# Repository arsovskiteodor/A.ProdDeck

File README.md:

# ProdDeck

Custom PCB productivity deck — StreamDeck-style device with key switches, rotary encoders, and a slider. Targets editors, designers, and video editors.

A joint project with product design student **Aleksandra Elin** ([LinkedIn](https://www.linkedin.com/in/aleksandra-elin-6274052a9/)).

**Hardware:**
- 6x key switches — Gateron KS-33 (Low Profile 2.0)
- 3x rotary encoders with push button — Bourns PEC11R-4220F-S0024
- 1x slider (fader) — Bourns PTA6043-2015DPB103
- MCU — STM32WB55CGU6 (BLE + native USB)
- USB-C (wired HID + charging) and LiPo battery (wireless BLE HID)

## PCB

| 3D view (top) | Layout |
|---|---|
|  |  |

## Repository Layout

| Folder | Contents |
|---|---|
| `KiCAD/ProdDeck/` | Schematic and PCB layout (KiCad 10), project libraries in `libs/`, fabrication outputs in `fab/` |
| `firmware/` | MCU firmware (ZMK) |
| `app/` | Desktop configurator — maps keys/dials/slider to shortcuts and app profiles |
| `enclosure/` | 3D mechanical files for chassis/panel |
| `docs/` | Component specs, schematic plan, datasheet notes |

## Status

| Area | Status |
|---|---|
| Component selection | Done |
| Schematic | Done |
| PCB layout | Done — 4-layer, 117 x 77 mm, fully routed, DRC clean |
| Fabrication outputs | Generated — Gerbers, drill, BOM and JLCPCB CPL in `KiCAD/ProdDeck/fab/` |
| Firmware | Not started — framework chosen (ZMK); board definition still to be written |
| Configurator app | Not started — stack not yet decided (Tauri vs Electron) |
| Enclosure | Not started — CAD tool not yet decided |

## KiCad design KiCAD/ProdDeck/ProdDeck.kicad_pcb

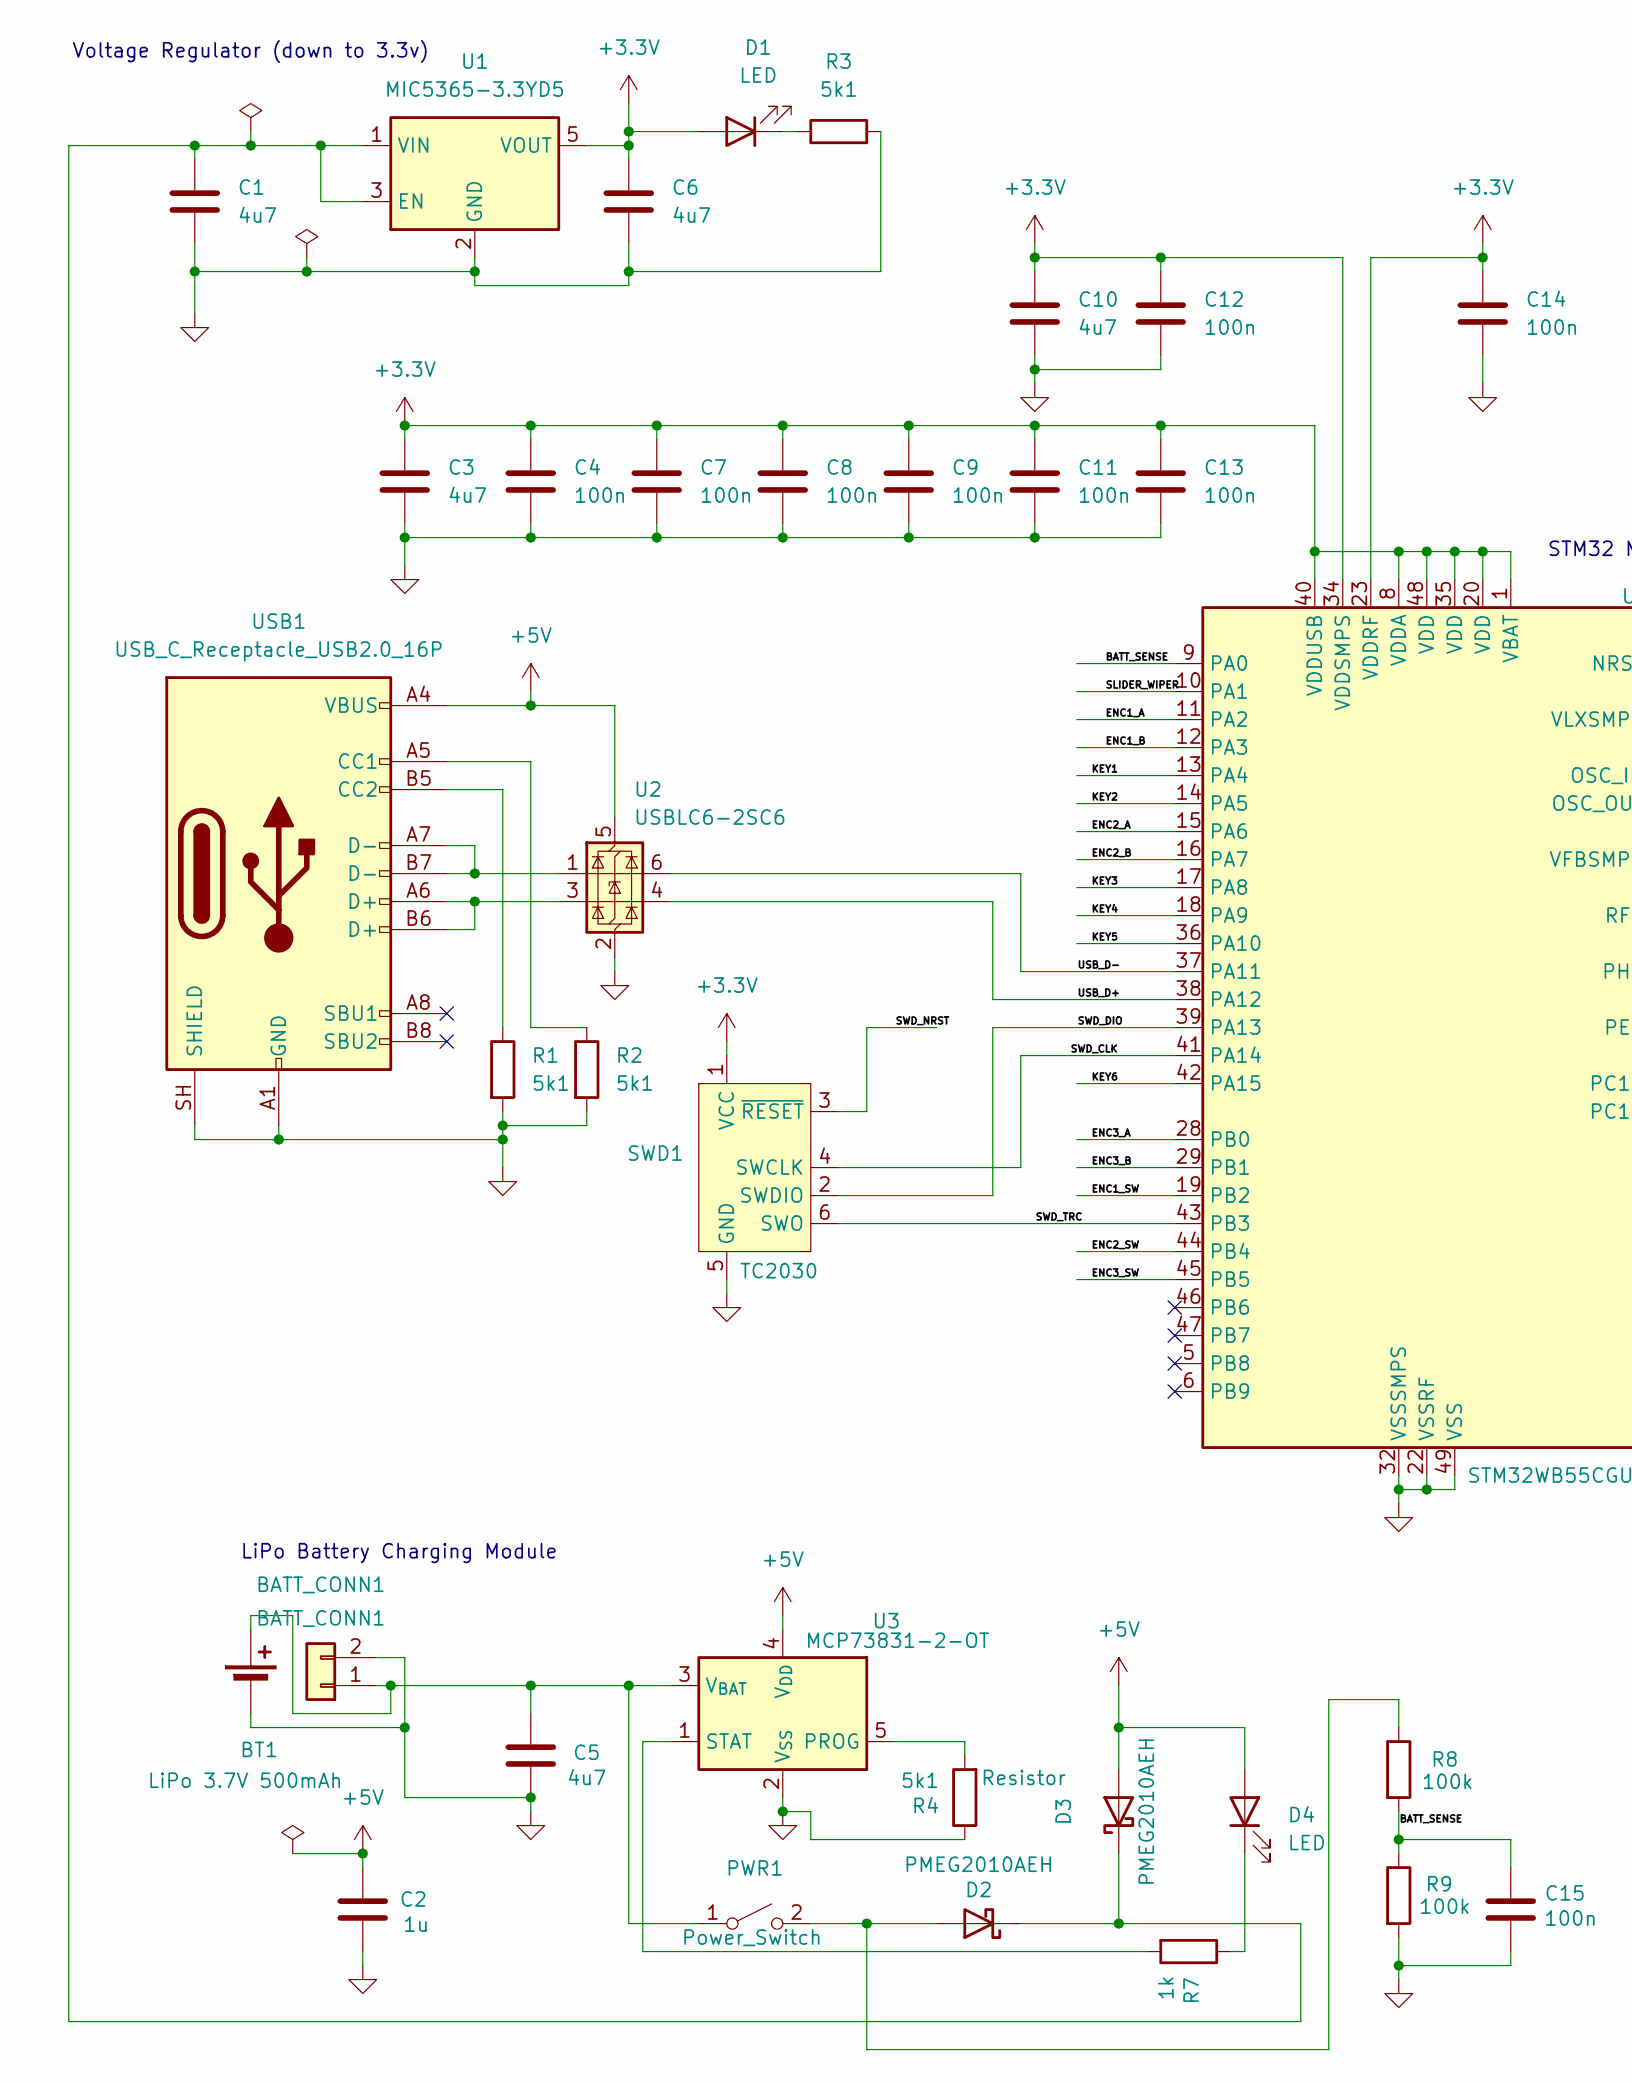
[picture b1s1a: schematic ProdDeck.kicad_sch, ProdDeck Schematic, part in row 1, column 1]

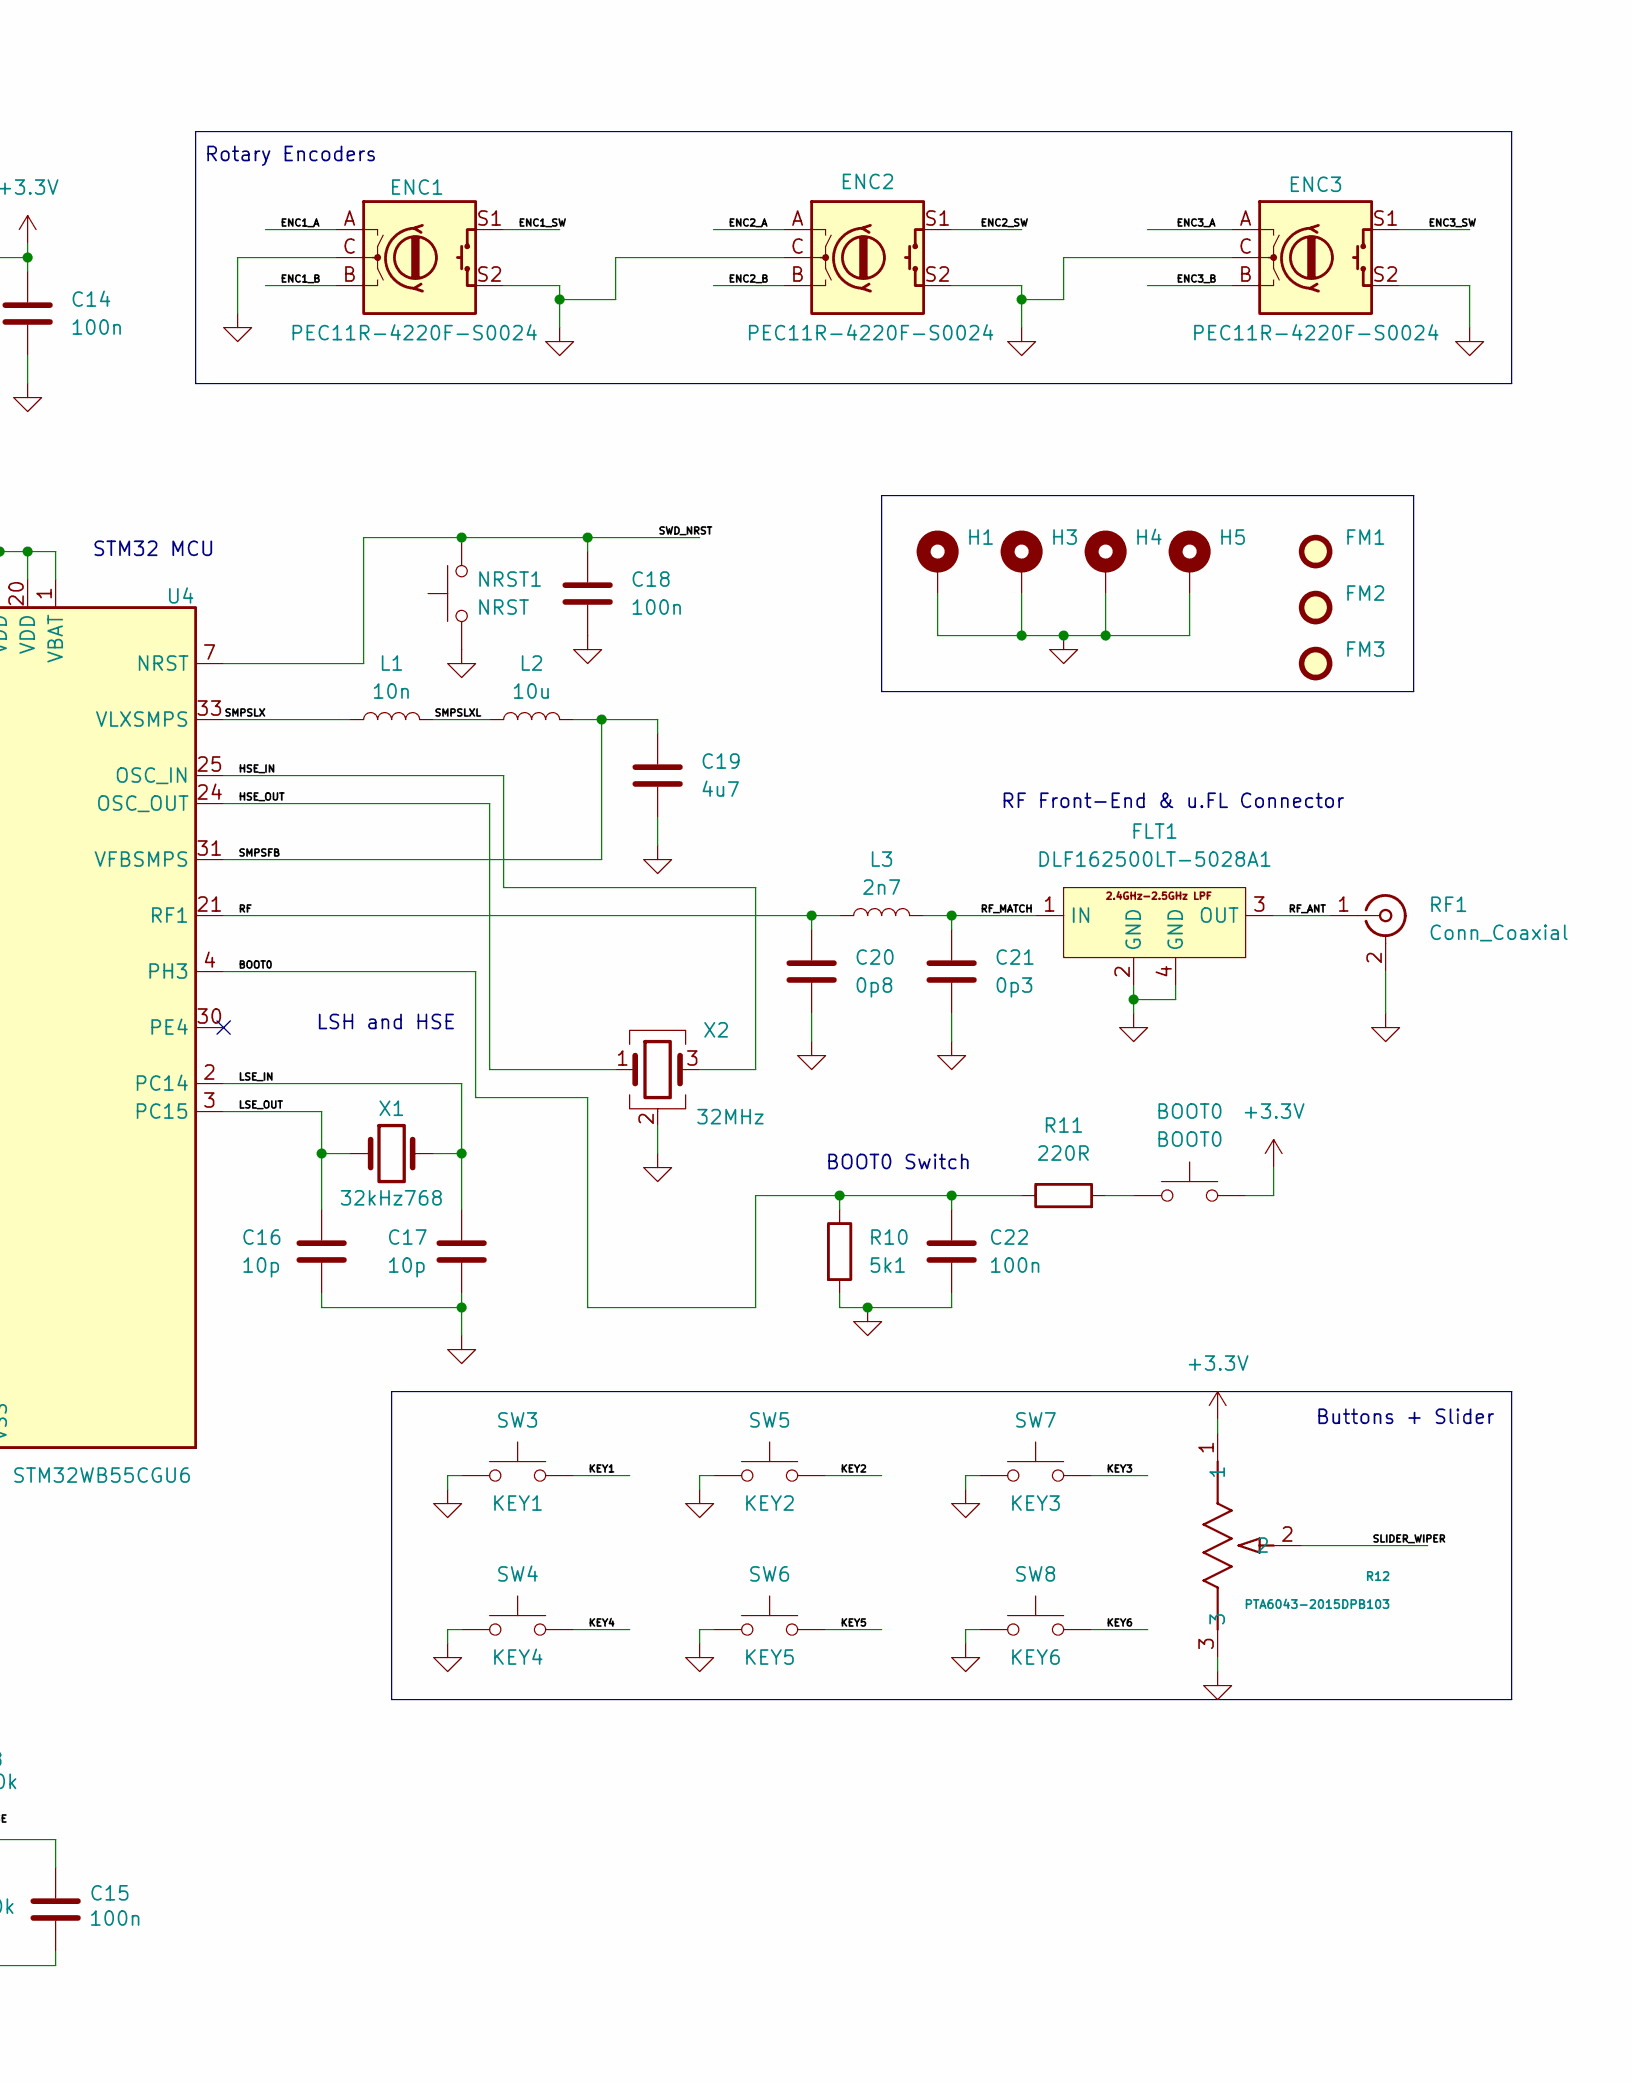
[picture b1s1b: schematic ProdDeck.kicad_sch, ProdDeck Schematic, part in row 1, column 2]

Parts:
BATT_CONN1: BATT_CONN1; JST_PH_S2B-PH-K_1x02_P2.00mm_Horizontal; Manufacturer Part Number S2B-PH-K-S(LF)(SN)
BOOT0: BOOT0; SW_SPST_CK_RS282G05A3; Manufacturer Part Number RS-282G05A3-SM RT
BT1: LiPo 3.7V 500mAh
C1, C3, C5, C6, C10, C19: 4u7; C_0603_1608Metric; Manufacturer Part Number 0603YD475MAT2A
C2: 1u; C_0402_1005Metric; Manufacturer Part Number 0402ZD105KAT2A
C4, C7, C8, C9, C11, C12, C13, C14, C15, C18, C22: 100n; C_0402_1005Metric; Manufacturer Part Number 04023C104KAT2A
C16, C17: 10p; C_0402_1005Metric; Manufacturer Part Number 04025A100JAT4A
C20: 0p8; C_0402_1005Metric; Manufacturer Part Number GRM1555C1HR80BA01D
C21: 0p3; C_0402_1005Metric; Manufacturer Part Number GRM1555C1HR30WA01D
D1, D4: LED; LED_0402_1005Metric; Manufacturer Part Number 150040RS73240
D2, D3: PMEG2010AEH; D_SOD-123; Manufacturer Part Number PMEG2010AEH,115
ENC1, ENC2, ENC3: PEC11R-4220F-S0024; Bourns-PEC11R-4220F-S0024-0-0-0
FLT1: DLF162500LT-5028A1; Manufacturer Part Number DLF162500LT-5028A1
FM1, FM2, FM3: Fiducial; Fiducial_1mm_Mask2mm
H1, H3, H4, H5: MountingHole_Pad; MountingHole_3.2mm_M3_Pad
L1: 10n; L_0402_1005Metric; Manufacturer Part Number LQG15WZ10NJ02D
L2: 10u; L_0805_2012Metric; Manufacturer Part Number LQM21FN100M80L
L3: 2n7; L_0402_1005Metric; Manufacturer Part Number LQG15HS2N7S02D
NRST1: NRST; SW_SPST_CK_RS282G05A3; Manufacturer Part Number RS-282G05A3-SM RT
PWR1: Power_Switch; SW_Slide_SPDT_Straight_CK_OS102011MS2Q; Manufacturer Part Number OS102011MS2QN1
R1, R2, R3, R4, R10: 5k1; R_0402_1005Metric; Manufacturer Part Number RC0402FR-075K1L
R7: 1k; R_0402_1005Metric; Manufacturer Part Number RC0402FR-071KL
R8, R9: 100k; R_0402_1005Metric; Manufacturer Part Number RC0402FR-07100KL
R11: 220R; R_0402_1005Metric; Manufacturer Part Number RC0402FR-07221RL
R12: PTA6043-2015DPB103; POT_PTA6043
RF1: Conn_Coaxial; U.FL_Hirose_U.FL-R-SMT-1_Vertical; Manufacturer Part Number U.FL-R-SMT(01)
SW3: KEY1; Gateron-KS33-Solderable-1U
SW4: KEY4; Gateron-KS33-Solderable-1U
SW5: KEY2; Gateron-KS33-Solderable-1U
SW6: KEY5; Gateron-KS33-Solderable-1U
SW7: KEY3; Gateron-KS33-Solderable-1U
SW8: KEY6; Gateron-KS33-Solderable-1U
SWD1: TC2030; Tag-Connect_TC2030-IDC-FP_2x03_P1.27mm_Vertical
U1: MIC5365-3.3YD5; TSOT-23-5; Manufacturer Part Number MIC5365-3.3YD5-TR
U2: USBLC6-2SC6; SOT-23-6; Manufacturer Part Number USBLC6-2SC6
U3: MCP73831-2-OT; SOT-23-5; Manufacturer Part Number MCP73831T-2ACI/OT
U4: STM32WB55CGU6; QFN-48-1EP_7x7mm_P0.5mm_EP5.6x5.6mm; Manufacturer Part Number STM32WB55CGU6
USB1: USB_C_Receptacle_USB2.0_16P; USB_C_Receptacle_GCT_USB4105-xx-A_16P_TopMnt_Horizontal; Manufacturer Part Number USB4105-GF-A
X1: 32kHz768; Crystal_SMD_2012-2Pin_2.0x1.2mm; Manufacturer Part Number STDMUB1-32.768K
X2: 32MHz; Crystal_SMD_2016-4Pin_2.0x1.6mm; Manufacturer Part Number NX2016SA-32M-EXS00A-CS06465

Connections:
+3.3V: BOOT0.2, C3.1, C4.1, C6.1, C7.1, C8.1, C9.1, C10.1, C11.1, C12.1, C13.1, C14.1, D1.2 (A), R12.1, SWD1.1 (VCC), U1.5 (VOUT), U4.1 (VBAT), U4.8 (VDDA), U4.20 (VDD), U4.23 (VDDRF), U4.34 (VDDSMPS), U4.35 (VDD), U4.40 (VDDUSB), U4.48 (VDD)
+5V: C2.1, D3.2 (A), D4.2 (A), U2.5 (VBUS), U3.4 (V_{DD}), USB1.A4 (VBUS), USB1.A9 (VBUS), USB1.B4 (VBUS), USB1.B9 (VBUS)
/BATT_SENSE: C15.1, R8.2, R9.1, U4.9 (PA0)
/BOOT0: C22.1, R10.1, R11.1, U4.4 (PH3)
/ENC1_A: ENC1.A, U4.11 (PA2)
/ENC1_B: ENC1.B, U4.12 (PA3)
/ENC1_SW: ENC1.S1, U4.19 (PB2)
/ENC2_A: ENC2.A, U4.15 (PA6)
/ENC2_B: ENC2.B, U4.16 (PA7)
/ENC2_SW: ENC2.S1, U4.44 (PB4)
/ENC3_A: ENC3.A, U4.28 (PB0)
/ENC3_B: ENC3.B, U4.29 (PB1)
/ENC3_SW: ENC3.S1, U4.45 (PB5)
/HSE_IN: U4.25 (OSC_IN), X2.3
/HSE_OUT: U4.24 (OSC_OUT), X2.1
/KEY1: SW3.2, U4.13 (PA4)
/KEY2: SW5.2, U4.14 (PA5)
/KEY3: SW7.2, U4.17 (PA8)
/KEY4: SW4.2, U4.18 (PA9)
/KEY5: SW6.2, U4.36 (PA10)
/KEY6: SW8.2, U4.42 (PA15)
/LSE_IN: C17.1, U4.2 (PC14), X1.2
/LSE_OUT: C16.1, U4.3 (PC15), X1.1
/RF: C20.1, L3.1, U4.21 (RF1)
/RF_ANT: FLT1.3 (OUT), RF1.1 (In)
/RF_MATCH: C21.1, FLT1.1 (IN), L3.2
/SLIDER_WIPER: R12.2, U4.10 (PA1)
/SMPSFB: C19.1, L2.2, U4.31 (VFBSMPS)
/SMPSLX: L1.1, U4.33 (VLXSMPS)
/SMPSLXL: L1.2, L2.1
/SWD_CLK: SWD1.4 (SWCLK), U4.41 (PA14)
/SWD_DIO: SWD1.2 (SWDIO), U4.39 (PA13)
/SWD_NRST: C18.1, NRST1.2, SWD1.3 (~RESET), U4.7 (NRST)
/SWD_TRC: SWD1.6 (SWO), U4.43 (PB3)
/USB_D+: U2.4 (I/O2), U4.38 (PA12)
/USB_D-: U2.6 (I/O1), U4.37 (PA11)
GND: BATT_CONN1.2, BT1.2 (-), C1.2, C2.2, C3.2, C4.2, C5.2, C6.2, C7.2, C8.2, C9.2, C10.2, C11.2, C12.2, C13.2, C14.2, C15.2, C16.2, C17.2, C18.2, C19.2, C20.2, C21.2, C22.2, ENC1.C, ENC1.S2, ENC2.C, ENC2.S2, ENC3.C, ENC3.S2, FLT1.2 (GND), FLT1.4 (GND), H1.1 (1_1), H3.1 (1_1), H4.1 (1_1), H5.1 (1_1), NRST1.1, R1.2, R2.2, R3.2, R4.1, R9.2, R10.2, R12.3, RF1.2 (Ext), SW3.1, SW4.1, SW5.1, SW6.1, SW7.1, SW8.1, SWD1.5 (GND), U1.2 (GND), U2.2 (GND), U3.2 (V_{SS}), U4.22 (VSSRF), U4.32 (VSSSMPS), U4.49 (VSS), USB1.A1 (GND), USB1.A12 (GND), USB1.B1 (GND), USB1.B12 (GND), USB1.SH (SHIELD), X2.2 (G), X2.4 (G)
unnamed: BATT_CONN1.1, BT1.1 (+), C5.1, PWR1.1 (A), U3.3 (V_{BAT})
unnamed: BOOT0.1, R11.2
unnamed: D1.1 (K), R3.1
unnamed: D2.2 (A), PWR1.2 (B), R8.1
unnamed: C1.1, D2.1 (K), D3.1 (K), U1.1 (VIN), U1.3 (EN)
unnamed: D4.1 (K), R7.1
unnamed: U2.1 (I/O1), USB1.A7 (D-), USB1.B7 (D-)
unnamed: U2.3 (I/O2), USB1.A6 (D+), USB1.B6 (D+)
unnamed: R4.2, U3.5 (PROG)
unnamed: R7.2, U3.1 (STAT)
unnamed: R2.1, USB1.A5 (CC1)
unnamed: R1.1, USB1.B5 (CC2)

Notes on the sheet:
Rotary Encoders
BOOT0 Switch
Buttons + Slider
STM32 MCU
LiPo Battery Charging Module
RF Front-End & u.FL Connector
Voltage Regulator (down to 3.3v)
LSH and HSE

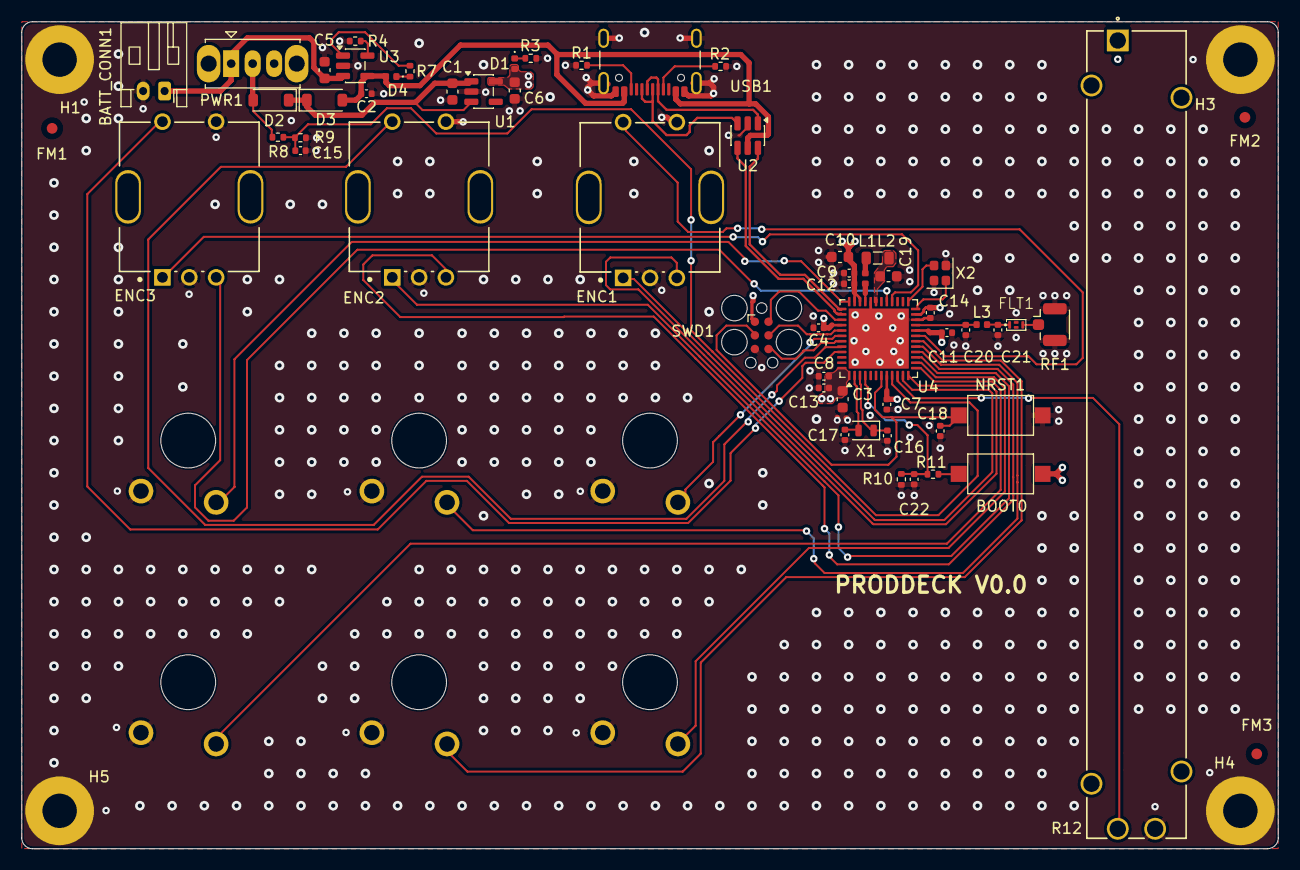
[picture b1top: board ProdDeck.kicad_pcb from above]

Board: 4 copper layers, 117.0 x 77.0 mm, 69 parts (0 on the bottom side), 49 nets.

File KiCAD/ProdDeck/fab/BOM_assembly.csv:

"Designator","Value","Footprint","Manufacturer","MPN","Qty"
"BOOT0","BOOT0","Button_Switch_SMD:SW_SPST_CK_RS282G05A3","C&K","RS-282G05A3-SM RT","1"
"C1,C3,C5,C6,C10,C19","4u7","Capacitor_SMD:C_0603_1608Metric","KYOCERA AVX","0603YD475MAT2A","6"
"C2","1u","Capacitor_SMD:C_0402_1005Metric","KYOCERA AVX","0402ZD105KAT2A","1"
"C4,C7,C8,C9,C11,C12,C13,C14,C15,C18,C22","100n","Capacitor_SMD:C_0402_1005Metric","KYOCERA AVX","04023C104KAT2A","11"
"C16,C17","10p","Capacitor_SMD:C_0402_1005Metric","KYOCERA AVX","04025A100JAT4A","2"
"C20","0p8","Capacitor_SMD:C_0402_1005Metric","Murata Electronics","GRM1555C1HR80BA01D","1"
"C21","0p3","Capacitor_SMD:C_0402_1005Metric","Murata Electronics","GRM1555C1HR30WA01D","1"
"D1,D4","LED","LED_SMD:LED_0402_1005Metric","Wurth Elektronik","150040RS73240","2"
"D2,D3","PMEG2010AEH","Diode_SMD:D_SOD-123","Nexperia","PMEG2010AEH,115","2"
"FLT1","DLF162500LT-5028A1","ProdDeck_PCBlib:DLF162500LT-5028A1","TDK","DLF162500LT-5028A1","1"
"L1","10n","Inductor_SMD:L_0402_1005Metric","Murata Electronics","LQG15WZ10NJ02D","1"
"L2","10u","Inductor_SMD:L_0805_2012Metric","Murata Electronics","LQM21FN100M80L","1"
"L3","2n7","Inductor_SMD:L_0402_1005Metric","Murata Electronics","LQG15HS2N7S02D","1"
"NRST1","NRST","Button_Switch_SMD:SW_SPST_CK_RS282G05A3","C&K","RS-282G05A3-SM RT","1"
"R1,R2,R3,R4,R10","5k1","Resistor_SMD:R_0402_1005Metric","YAGEO","RC0402FR-075K1L","5"
"R7","1k","Resistor_SMD:R_0402_1005Metric","YAGEO","RC0402FR-071KL","1"
"R8,R9","100k","Resistor_SMD:R_0402_1005Metric","YAGEO","RC0402FR-07100KL","2"
"R11","220R","Resistor_SMD:R_0402_1005Metric","YAGEO","RC0402FR-07221RL","1"
"RF1","Conn_Coaxial","Connector_Coaxial:U.FL_Hirose_U.FL-R-SMT-1_Vertical","Hirose Connector","U.FL-R-SMT(01)","1"
"U1","MIC5365-3.3YD5","Package_TO_SOT_SMD:TSOT-23-5","Microchip Technology","MIC5365-3.3YD5-TR","1"
"U2","USBLC6-2SC6","Package_TO_SOT_SMD:SOT-23-6","STMicroelectronics","USBLC6-2SC6 ","1"
"U3","MCP73831-2-OT","Package_TO_SOT_SMD:SOT-23-5","Microchip Technology","MCP73831T-2ACI/OT","1"
"U4","STM32WB55CGU6","Package_DFN_QFN:QFN-48-1EP_7x7mm_P0.5mm_EP5.6x5.6mm","STMicroelectronics","STM32WB55CGU6","1"
"USB1","USB_C_Receptacle_USB2.0_16P","Connector_USB:USB_C_Receptacle_GCT_USB4105-xx-A_16P_TopMnt_Horizontal","GCT","USB4105-GF-A","1"
"X1","32kHz768","Crystal:Crystal_SMD_2012-2Pin_2.0x1.2mm","NDK (NIHON DEMPA KOGYO CO., LTD)","STDMUB1-32.768K","1"
"X2","32MHz","Crystal:Crystal_SMD_2016-4Pin_2.0x1.6mm","NDK","NX2016SA-32M-EXS00A-CS06465","1"
